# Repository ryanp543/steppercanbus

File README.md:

# CANBus Controlled Stepper Motor Driver 

## Overview

This repository contains the Autodesk Eagle schematic and layout for the custom stepper motor driver developed for the robotic arm mounted on the MIT Bioinstrumentation Lab rover. This information is found in the `Stepper CANBus V2` folder.

The driver had to be able to 1) fit in a CANBus network, 2) require the fewest numbers of wires to operate (in this case, power, ground, and the two CANBus lines), and 3) run on 21 V. What resulted from these constraints is a stepper driver that can be used universally with 24 V bipolar stepper motors and can be easily modified via the interface of the mounted Teensy. Despite the fact that the PCB shape is tailored to this robotic arm, multiple of these drivers can be linked together in any desired daisy chained CANBus network, as long as the last driver in the chain has the switch turned on to activate the 120 Ohm terminator resistor.

The microcontroller chosen for this driver was a Teensy 3.2 based on its widely used interface, easy customization, and relatively small size for a breakout board microcontroller. A Texas Instruments DRV8825 microstepper driver carrier board was selected so it could also be easily mounted onto the custom PCB and take commands from the Teensy. For the step-down power converter, a buck switching regulator (specifically Texas Instruments chip LM2594MX-5.0/NOPBCT-ND) was picked to provide a fixed 500 mA at 5 V, stepped down from an input voltage of around 20 to 24 V. External components such as capacitors and diodes were placed in the external circuit according to the data sheet.

The firmware that is uploaded to the Teensy from the Arduino IDE can be found in the `Stepper_CANBus_Firmware` directory. 

## Contributors

#### Primary Contributors
Ryan Poon from the [MIT Bioinstrumentation Lab](https://bioinstrumentation.mit.edu/) is the primary contributor of this project.

#### Other Contributors
Professor Ian Hunter served as the main advisor.

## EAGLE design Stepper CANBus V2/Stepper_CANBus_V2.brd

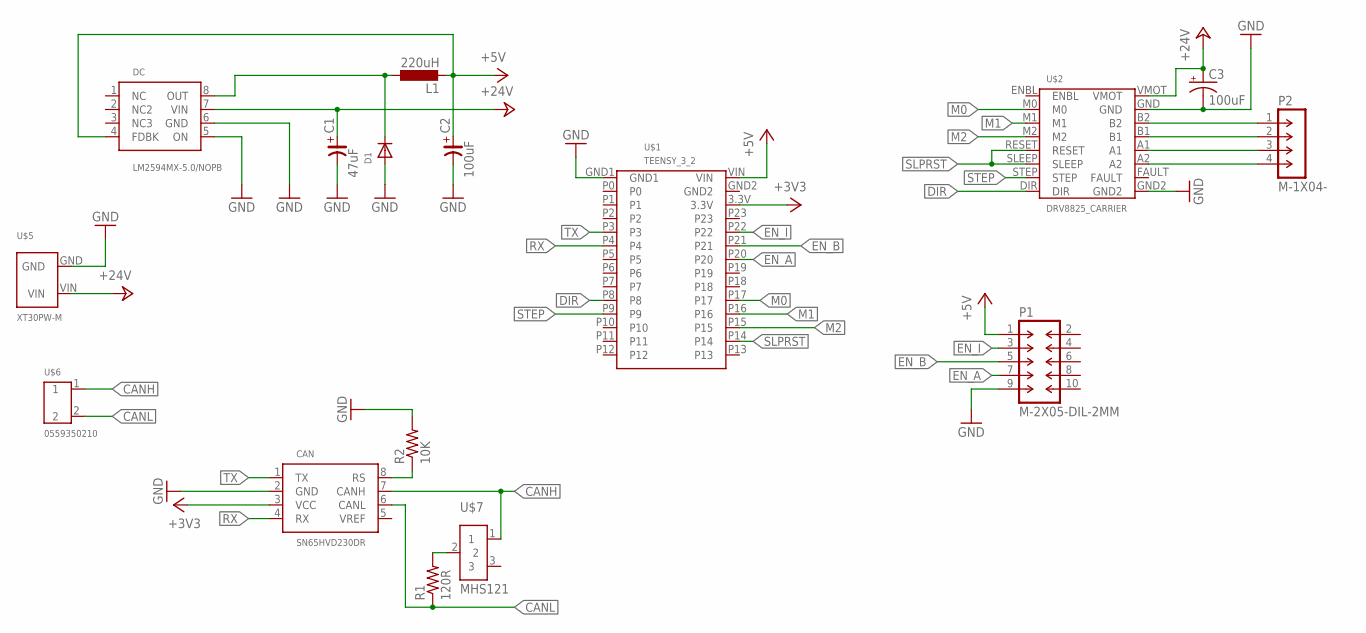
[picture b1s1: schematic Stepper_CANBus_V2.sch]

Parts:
C1: 47uF; C7343/T
C2: 100uF; C7343/T
C3: 100uF; E2,5-7
CAN: SN65HVD230DR; SOIC8
D1: DIODESOD-323F; SOD-323F
DC: LM2594MX-5.0/NOPB; SOIC8
L1: 220uH; L4532M
P1: M-2X05-DIL-2MM; DIL-2MM-2X05
P2: M-1X04-; DIL-2MM-1X04
R1: 120R; R0603
R2: 10K; R0603
U$1: TEENSY_3_2
U$2: DRV8825_CARRIER
U$5: XT30PW-M
U$6: 0559350210
U$7: MHS121

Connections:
+3V3: CAN.3 (VCC), U$1.3.3V
+5V: C2.+, DC.4 (FDBK), L1.2, P1.1, U$1.VIN
+24V: C1.+, C3.+, DC.7 (VIN), U$2.VMOT, U$5.VIN
CANH: CAN.7 (CANH), U$6.1, U$7.1
CANL: CAN.6 (CANL), R1.1, U$6.2
DIR: U$1.P8, U$2.DIR
EN_A: P1.7, U$1.P20
EN_B: P1.5, U$1.P21
EN_I: P1.3, U$1.P22
GND: C1.-, C2.-, C3.-, CAN.2 (GND), D1.A, DC.5 (ON), DC.6 (GND), P1.9, R2.2, U$1.GND1, U$2.GND, U$2.GND2, U$5.GND
M0: U$1.P17, U$2.M0
M1: U$1.P16, U$2.M1
M2: U$1.P15, U$2.M2
unnamed: CAN.8 (RS), R2.1
unnamed: D1.C, DC.8 (OUT), L1.1
unnamed: P2.1, U$2.B2
unnamed: R1.2, U$7.2
unnamed: P2.2, U$2.B1
unnamed: P2.3, U$2.A1
unnamed: P2.4, U$2.A2
RX: CAN.4 (RX), U$1.P4
SLPRST: U$1.P14, U$2.RESET, U$2.SLEEP
STEP: U$1.P9, U$2.STEP
TX: CAN.1 (TX), U$1.P3

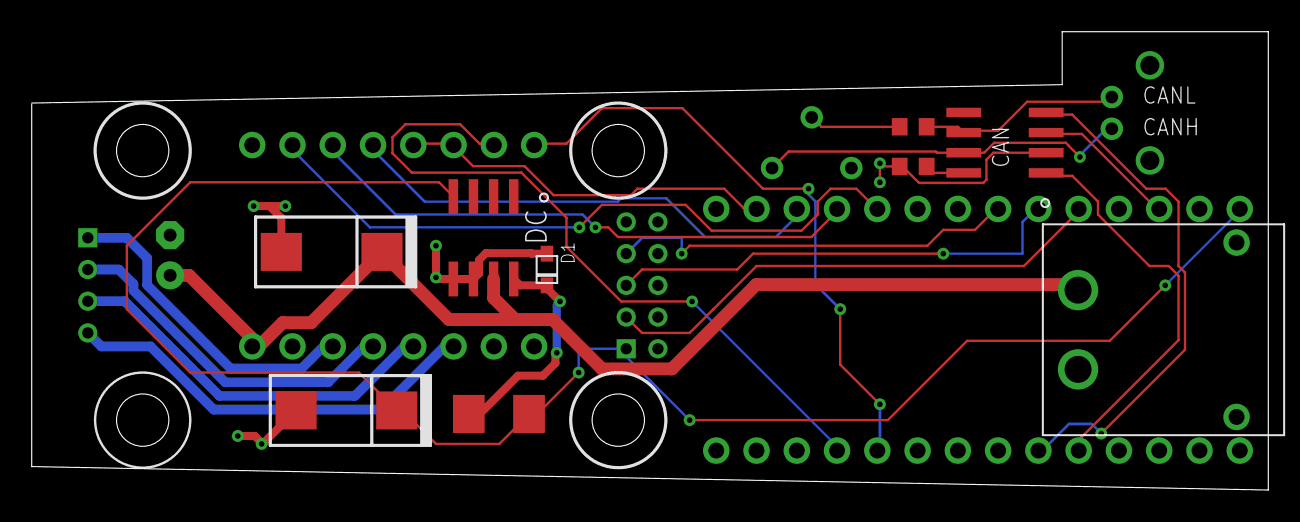
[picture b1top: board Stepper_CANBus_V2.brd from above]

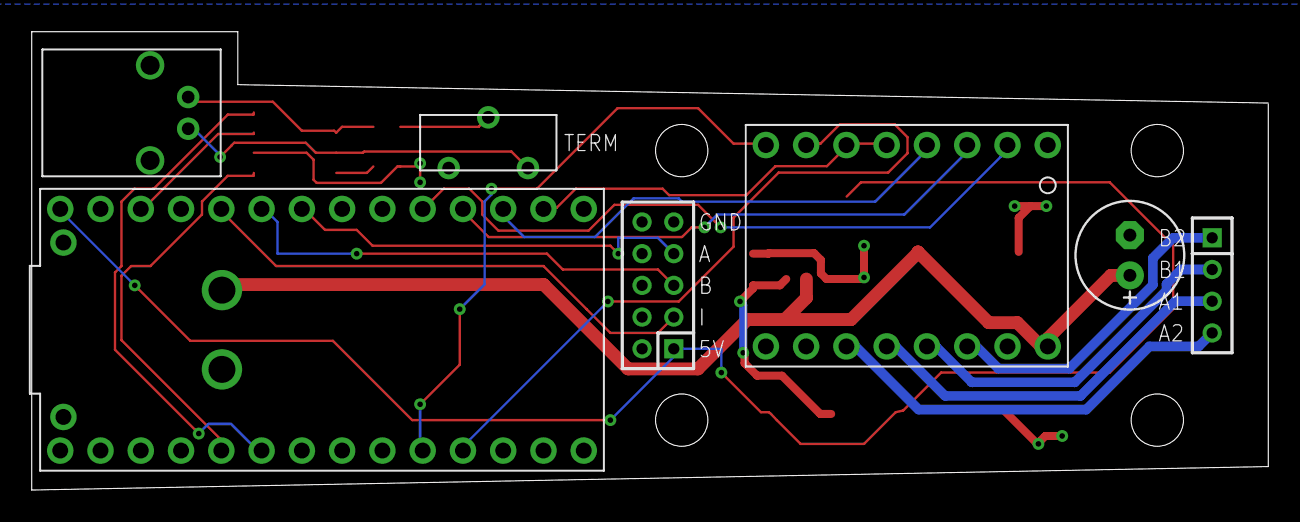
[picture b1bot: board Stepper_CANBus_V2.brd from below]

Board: 2 copper layers, 78.0 x 28.9 mm, 16 parts (7 on the bottom side), 24 nets.

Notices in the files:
parts and their libraries:
rc-master: Copyright (C) 2007, Bob Starr
con-headers-jp: Copyright (C) 2008, Bob Starr
